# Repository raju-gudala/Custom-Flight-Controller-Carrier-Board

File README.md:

# Custom Flight Controller Carrier Board

A custom carrier board designed to support the **Pixhawk Cube Orange+** flight controller. The primary objective of this design is to provide a more **ergonomic, organized, and user-friendly interface for port connections**, making it easier to integrate the flight controller with external sensors, peripherals, communication interfaces, and other UAV systems.

The complete hardware design, including schematic capture and PCB layout, was developed using **KiCad**.

## Features

* Custom carrier board designed for **Pixhawk Cube Orange+**
* Ergonomically arranged connectors for easier system integration
* Organized port connections for improved accessibility and wiring
* Custom PCB layout optimized around the Cube Orange+ form factor
* Custom footprints and symbols included for project-specific components
* Complete schematic and PCB design developed in KiCad
* Designed for UAV and flight-control system integration
* Includes PCB visualization images for reference

## Design Overview

The carrier board acts as an interface between the **Pixhawk Cube Orange+** flight controller and external UAV peripherals.

Instead of connecting multiple peripherals directly to the flight controller in a tightly packed arrangement, the carrier board brings the required interfaces to more accessible locations on the PCB. This provides a cleaner wiring arrangement and makes the overall flight-control system easier to assemble, inspect, and maintain.

### Key Design Objectives

* **Ergonomics** — Position commonly used connectors where they are easily accessible.
* **Ease of Integration** — Simplify connections between the Cube Orange+ and external peripherals.
* **Serviceability** — Make wiring, troubleshooting, and maintenance easier.
* **Compact Integration** — Provide a dedicated carrier PCB around the Cube Orange+.
* **Customizability** — Allow the carrier board to be adapted for specific UAV applications.

## Hardware

The board is designed around the **Pixhawk Cube Orange+** flight controller and provides the required physical interface between the flight controller and connected UAV peripherals.

The design includes:

* Cube Orange+ carrier interface
* External peripheral connectors
* Custom connector footprints
* Custom symbols and footprints
* PCB mounting and mechanical interface
* Organized signal and power routing

## Repository Contents

```text
├── Custom Footprints/              # Custom KiCad footprints, symbols and 3D models
├── carrier_board_foot.pretty/      # Project-specific PCB footprints
├── carrier_board_symbols.kicad_sym # Custom schematic symbols
├── fp-lib-table                    # KiCad footprint library configuration
├── Ti-Circle v1.0.kicad_pro        # KiCad project file
├── Ti-Circle v1.0.kicad_sch        # Schematic
├── Ti-Circle v1.0.kicad_pcb        # PCB layout
├── Ti-Circle v1.0_top.png          # Top-side PCB view
├── Ti-Circle v1.0_bottom.png       # Bottom-side PCB view
└── README.md
```

## PCB Layout

The PCB layout was developed with emphasis on:

* Ergonomic connector placement
* Accessible peripheral interfaces
* Clean signal routing
* Practical component placement
* Mechanical compatibility with the Cube Orange+
* Maintainable wiring and system integration

The top and bottom PCB renders are included in the repository for quick visual reference.

## Design Workflow

The complete design was developed using **KiCad**, covering the complete PCB design workflow:

```text
Design Requirements
       ↓
Schematic Design
       ↓
Component & Library Selection
       ↓
PCB Placement
       ↓
PCB Routing
       ↓
Design Verification
       ↓
3D / Layout Review
       ↓
Manufacturing Files
```

## Tools Used

* **KiCad** — Schematic capture, PCB layout, library management, and design verification

## Project Status

**Status:** Custom carrier board design completed.

The repository contains the KiCad schematic, PCB layout, custom libraries, footprints, and reference PCB images required to continue development or review the design.

## License

This project is currently provided for reference and development purposes. If you intend to reuse, modify, or distribute the design, please specify an appropriate open-source hardware license.

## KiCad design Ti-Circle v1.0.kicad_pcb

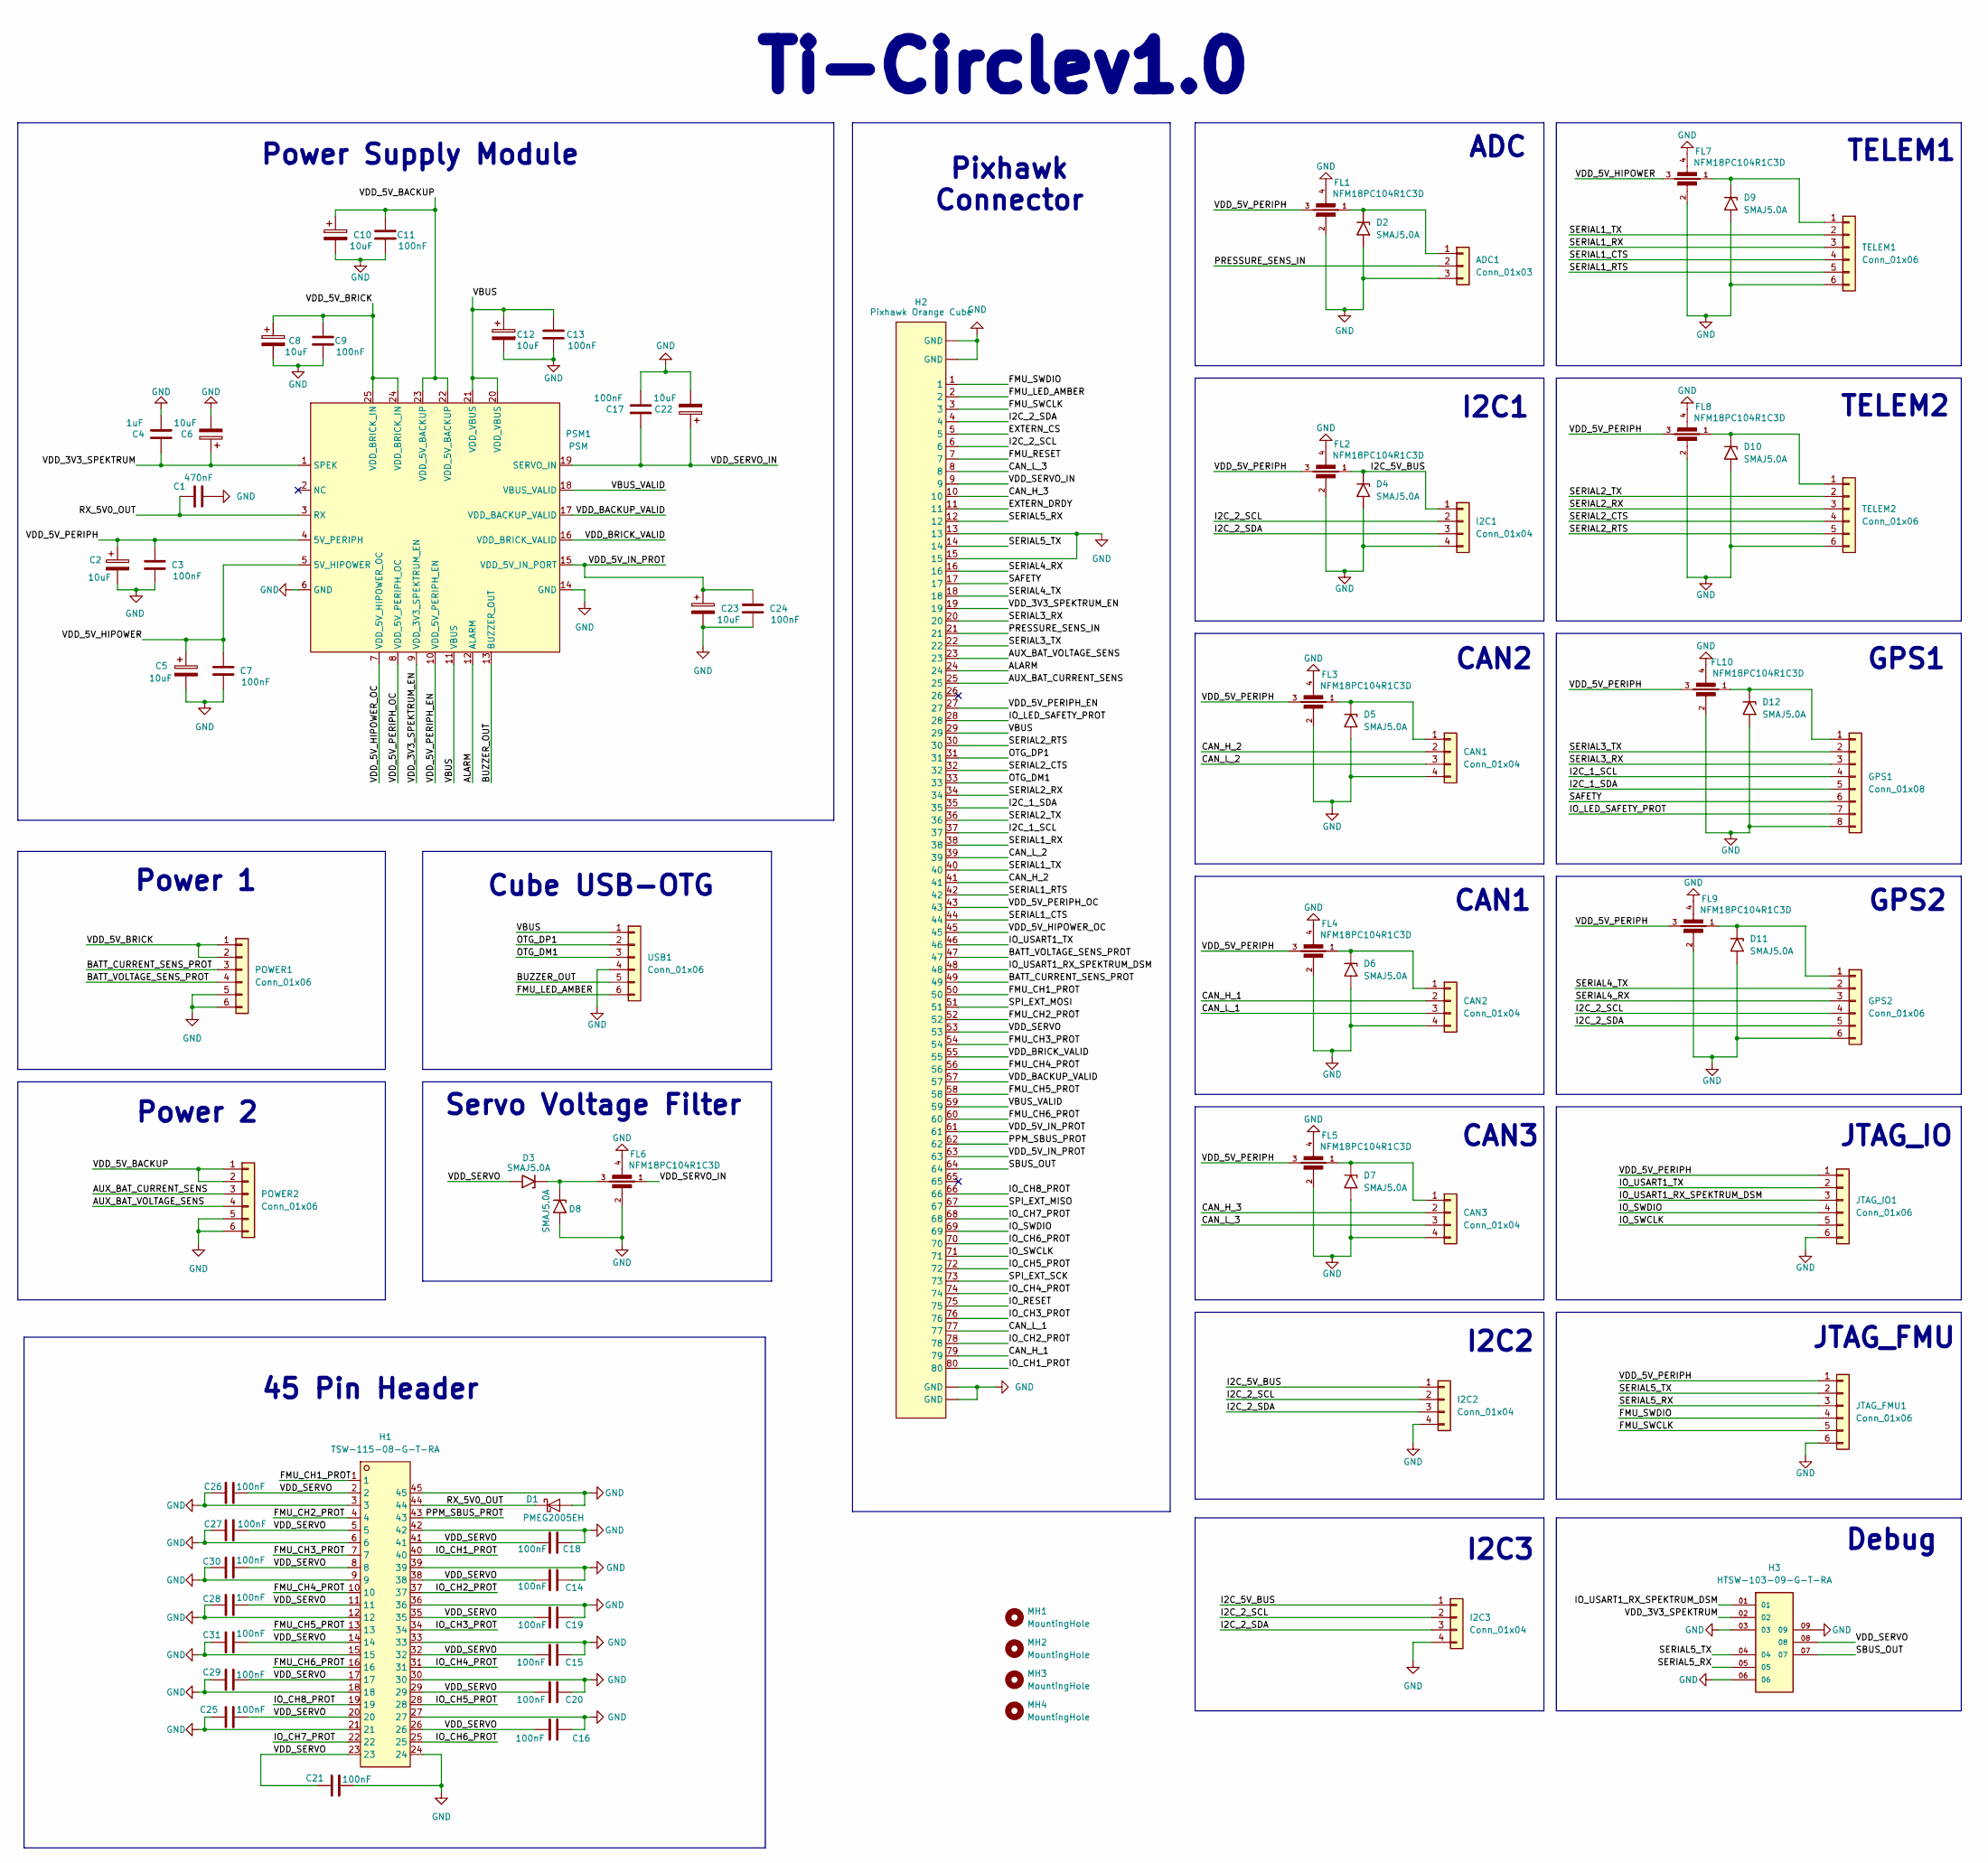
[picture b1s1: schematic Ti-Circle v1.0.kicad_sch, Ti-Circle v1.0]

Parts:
ADC1: Conn_01x03; JST_GH_SM03B-GHS-TB_1x03-1MP_P1.25mm_Horizontal
C1: 470nF; C_0603_1608Metric
C2, C5, C6, C8, C10, C12, C22, C23: 10uF; CAPPM6032X280N
C3, C7, C9, C11, C13, C14, C15, C16, C17, C18, C19, C20, C21, C24, C25, C26, C27, C28, C29, C30, C31: 100nF; C_0603_1608Metric
C4: 1uF; C_0805_2012Metric
CAN1, CAN2, CAN3: Conn_01x04; JST_GH_SM04B-GHS-TB_1x04-1MP_P1.25mm_Horizontal
D1: PMEG2005EH; SMFA2005CA
D2, D3, D4, D5, D6, D7, D8, D9, D10, D11, D12: SMAJ5.0A; DIOM5026X229N
FL1, FL2, FL3, FL4, FL5, FL6, FL7, FL8, FL9, FL10: NFM18PC104R1C3D; NFM18PC104R1C3D_MUR
GPS1: Conn_01x08; JST_GH_SM08B-GHS-TB_1x08-1MP_P1.25mm_Horizontal
GPS2: Conn_01x06; JST_GH_SM06B-GHS-TB_1x06-1MP_P1.25mm_Horizontal
H1: TSW-115-08-G-T-RA; HDRRA45W64P254_3X15_3810X254X810P
H2: Pixhawk Orange Cube; PIXHAWK CUBE ORANGE
H3: HTSW-103-09-G-T-RA; SAMTEC_HTSW-103-09-G-T-RA
I2C1, I2C2, I2C3: Conn_01x04; JST_GH_SM04B-GHS-TB_1x04-1MP_P1.25mm_Horizontal
JTAG_FMU1: Conn_01x06; JST_SUR_SM06B-SURS-TF_1x06-1MP_P0.80mm_Horizontal
JTAG_IO1: Conn_01x06; JST_SUR_SM06B-SURS-TF_1x06-1MP_P0.80mm_Horizontal
MH1, MH2, MH3, MH4: MountingHole; MountingHole_2.2mm_M2_DIN965_Pad_TopBottom
POWER1, POWER2: Conn_01x06; Molex_CLIK-Mate_502494-0670_1x06-1MP_P2.00mm_Horizontal
PSM1: PSM
TELEM1, TELEM2: Conn_01x06; JST_GH_SM06B-GHS-TB_1x06-1MP_P1.25mm_Horizontal
USB1: Conn_01x06; JST_GH_SM06B-GHS-TB_1x06-1MP_P1.25mm_Horizontal

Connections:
/ALARM: H2.24, PSM1.12 (ALARM)
/AUX_BAT_CURRENT_SENS: H2.25, POWER2.3
/AUX_BAT_VOLTAGE_SENS: H2.23, POWER2.4
/BATT_CURRENT_SENS_PROT: H2.49, POWER1.3
/BATT_VOLTAGE_SENS_PROT: H2.47, POWER1.4
/BUZZER_OUT: PSM1.13 (BUZZER_OUT), USB1.5
/CAN_H_1: CAN2.2, H2.79
/CAN_H_2: CAN1.2, H2.41
/CAN_H_3: CAN3.2, H2.10
/CAN_L_1: CAN2.3, H2.77
/CAN_L_2: CAN1.3, H2.39
/CAN_L_3: CAN3.3, H2.8
/EXTERN_CS: H2.5
/EXTERN_DRDY: H2.11
/FMU_CH1_PROT: H1.1, H2.50
/FMU_CH2_PROT: H1.4, H2.52
/FMU_CH3_PROT: H1.7, H2.54
/FMU_CH4_PROT: H1.10, H2.56
/FMU_CH5_PROT: H1.13, H2.58
/FMU_CH6_PROT: H1.16, H2.60
/FMU_LED_AMBER: H2.2, USB1.6
/FMU_RESET: H2.7
/FMU_SWCLK: H2.3, JTAG_FMU1.5
/FMU_SWDIO: H2.1, JTAG_FMU1.4
/I2C_1_SCL: GPS1.4, H2.37
/I2C_1_SDA: GPS1.5, H2.35
/I2C_2_SCL: GPS2.4, H2.6, I2C1.2, I2C2.2, I2C3.2
/I2C_2_SDA: GPS2.5, H2.4, I2C1.3, I2C2.3, I2C3.3
/I2C_5V_BUS: D4.1 (A1), FL2.1, I2C1.1, I2C2.1, I2C3.1
/IO_CH1_PROT: H1.40, H2.80
/IO_CH2_PROT: H1.37, H2.78
/IO_CH3_PROT: H1.34, H2.76
/IO_CH4_PROT: H1.31, H2.74
/IO_CH5_PROT: H1.28, H2.72
/IO_CH6_PROT: H1.25, H2.70
/IO_CH7_PROT: H1.22, H2.68
/IO_CH8_PROT: H1.19, H2.66
/IO_LED_SAFETY_PROT: GPS1.7, H2.28
/IO_RESET: H2.75
/IO_SWCLK: H2.71, JTAG_IO1.5
/IO_SWDIO: H2.69, JTAG_IO1.4
/IO_USART1_RX_SPEKTRUM_DSM: H2.48, H3.01, JTAG_IO1.3
/IO_USART1_TX: H2.46, JTAG_IO1.2
/OTG_DM1: H2.33, USB1.3
/OTG_DP1: H2.31, USB1.2
/PPM_SBUS_PROT: H1.43, H2.62
/PRESSURE_SENS_IN: ADC1.2, H2.21
/RX_5V0_OUT: C1.1, D1.1 (K), H1.44, PSM1.3 (RX)
/SAFETY: GPS1.6, H2.17
/SBUS_OUT: H2.64, H3.07
/SERIAL1_CTS: H2.44, TELEM1.4
/SERIAL1_RTS: H2.42, TELEM1.5
/SERIAL1_RX: H2.38, TELEM1.3
/SERIAL1_TX: H2.40, TELEM1.2
/SERIAL2_CTS: H2.32, TELEM2.4
/SERIAL2_RTS: H2.30, TELEM2.5
/SERIAL2_RX: H2.34, TELEM2.3
/SERIAL2_TX: H2.36, TELEM2.2
/SERIAL3_RX: GPS1.3, H2.20
/SERIAL3_TX: GPS1.2, H2.22
/SERIAL4_RX: GPS2.3, H2.16
/SERIAL4_TX: GPS2.2, H2.18
/SERIAL5_RX: H2.12, H3.05, JTAG_FMU1.3
/SERIAL5_TX: H2.14, H3.04, JTAG_FMU1.2
/SPI_EXT_MISO: H2.67
/SPI_EXT_MOSI: H2.51
/SPI_EXT_SCK: H2.73
/VBUS: C12.1, C13.1, H2.29, PSM1.11 (VBUS), PSM1.20 (VDD_VBUS), PSM1.21 (VDD_VBUS), USB1.1
/VBUS_VALID: H2.59, PSM1.18 (VBUS_VALID)
/VDD_3V3_SPEKTRUM: C4.1, C6.1, H3.02, PSM1.1 (SPEK)
/VDD_3V3_SPEKTRUM_EN: H2.19, PSM1.9 (VDD_3V3_SPEKTRUM_EN)
/VDD_5V_BACKUP: C10.1, C11.1, POWER2.1, POWER2.2, PSM1.22 (VDD_5V_BACKUP), PSM1.23 (VDD_5V_BACKUP)
/VDD_5V_BRICK: C8.1, C9.1, POWER1.1, POWER1.2, PSM1.24 (VDD_BRICK_IN), PSM1.25 (VDD_BRICK_IN)
/VDD_5V_HIPOWER: C5.1, C7.1, FL7.3, PSM1.5 (5V_HIPOWER)
/VDD_5V_HIPOWER_OC: H2.45, PSM1.7 (VDD_5V_HIPOWER_OC)
/VDD_5V_IN_PROT: C23.1, C24.1, H2.61, H2.63, PSM1.15 (VDD_5V_IN_PORT)
/VDD_5V_PERIPH: C2.1, C3.1, FL1.3, FL2.3, FL3.3, FL4.3, FL5.3, FL8.3, FL9.3, FL10.3, JTAG_FMU1.1, JTAG_IO1.1, PSM1.4 (5V_PERIPH)
/VDD_5V_PERIPH_EN: H2.27, PSM1.10 (VDD_5V_PERIPH_EN)
/VDD_5V_PERIPH_OC: H2.43, PSM1.8 (VDD_5V_PERIPH_OC)
/VDD_BACKUP_VALID: H2.57, PSM1.17 (VDD_BACKUP_VALID)
/VDD_BRICK_VALID: H2.55, PSM1.16 (VDD_BRICK_VALID)
/VDD_SERVO: C14.2, C15.2, C16.1, C18.2, C19.2, C20.2, C21.1, C25.2, C26.1, C27.1, C28.1, C29.1, C30.1, C31.1, D3.2 (A2), H1.2, H1.5, H1.8, H1.11, H1.14, H1.17, H1.20, H1.23, H1.26, H1.29, H1.32, H1.35, H1.38, H1.41, H2.53, H3.08
/VDD_SERVO_IN: C17.1, C22.1, FL6.1, H2.9, PSM1.19 (SERVO_IN)
GND: ADC1.3, C1.2, C2.2, C3.2, C4.2, C5.2, C6.2, C7.2, C8.2, C9.2, C10.2, C11.2, C12.2, C13.2, C14.1, C15.1, C16.2, C17.2, C18.1, C19.1, C20.1, C21.2, C22.2, C23.2, C24.2, C25.1, C26.2, C27.2, C28.2, C29.2, C30.2, C31.2, CAN1.4, CAN2.4, CAN3.4, D1.2 (A), D2.2 (A2), D4.2 (A2), D5.2 (A2), D6.2 (A2), D7.2 (A2), D8.2 (A2), D9.2 (A2), D10.2 (A2), D11.2 (A2), D12.2 (A2), FL1.2, FL1.4, FL2.2, FL2.4, FL3.2, FL3.4, FL4.2, FL4.4, FL5.2, FL5.4, FL6.2, FL6.4, FL7.2, FL7.4, FL8.2, FL8.4, FL9.2, FL9.4, FL10.2, FL10.4, GPS1.8, GPS2.6, H1.3, H1.6, H1.9, H1.12, H1.15, H1.18, H1.21, H1.24, H1.27, H1.30, H1.33, H1.36, H1.39, H1.42, H1.45, H2. (GND), H2.13, H2.15, H3.03, H3.06, H3.09, I2C1.4, I2C2.4, I2C3.4, JTAG_FMU1.6, JTAG_IO1.6, POWER1.5, POWER1.6, POWER2.5, POWER2.6, PSM1.6 (GND), PSM1.14 (GND), TELEM1.6, TELEM2.6, USB1.4
unnamed: ADC1.1, D2.1 (A1), FL1.1
unnamed: CAN1.1, D5.1 (A1), FL3.1
unnamed: CAN2.1, D6.1 (A1), FL4.1
unnamed: CAN3.1, D7.1 (A1), FL5.1
unnamed: D3.1 (A1), D8.1 (A1), FL6.3
unnamed: D9.1 (A1), FL7.1, TELEM1.1
unnamed: D10.1 (A1), FL8.1, TELEM2.1
unnamed: D11.1 (A1), FL9.1, GPS2.1
unnamed: D12.1 (A1), FL10.1, GPS1.1

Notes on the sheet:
CAN1
Power 1
GPS1
Cube USB-OTG
GPS2
Servo Voltage Filter
ADC
Debug
Pixhawk Connector
CAN3
TELEM1
I2C1
I2C3
Ti-Circlev1.0
Power Supply Module
I2C2
Power 2
JTAG_IO
45 Pin Header
JTAG_FMU
CAN2
TELEM2

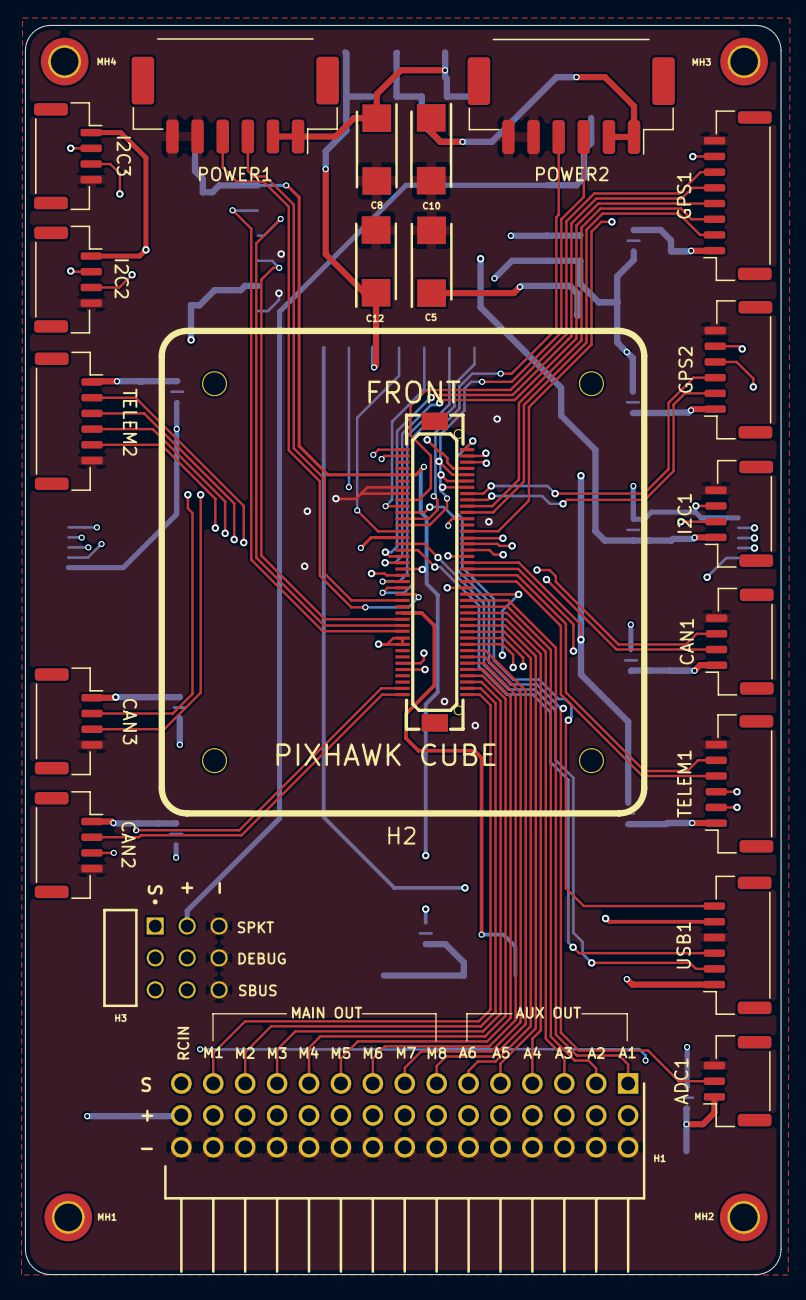
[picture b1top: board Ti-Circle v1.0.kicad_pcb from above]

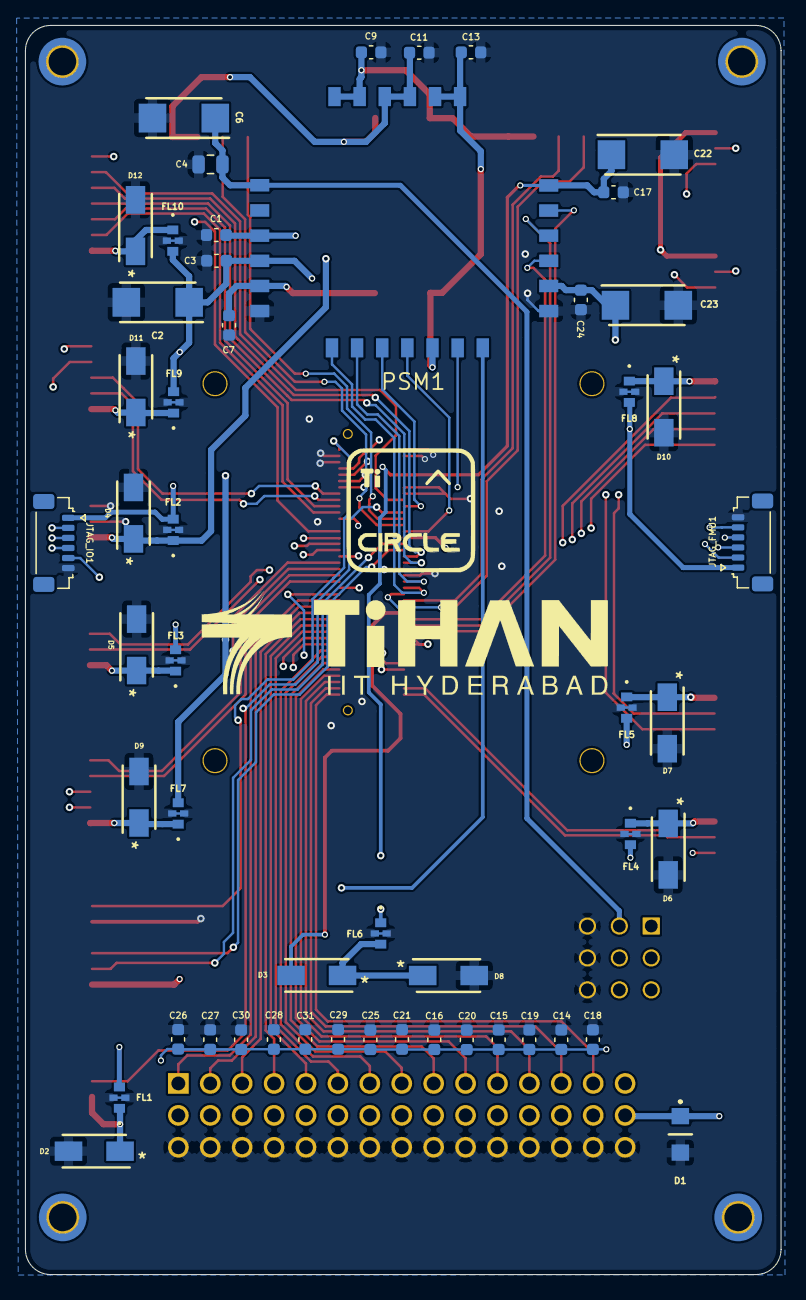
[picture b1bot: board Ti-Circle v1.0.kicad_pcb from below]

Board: 4 copper layers, 60.1 x 99.4 mm, 77 parts (52 on the bottom side), 86 nets.
